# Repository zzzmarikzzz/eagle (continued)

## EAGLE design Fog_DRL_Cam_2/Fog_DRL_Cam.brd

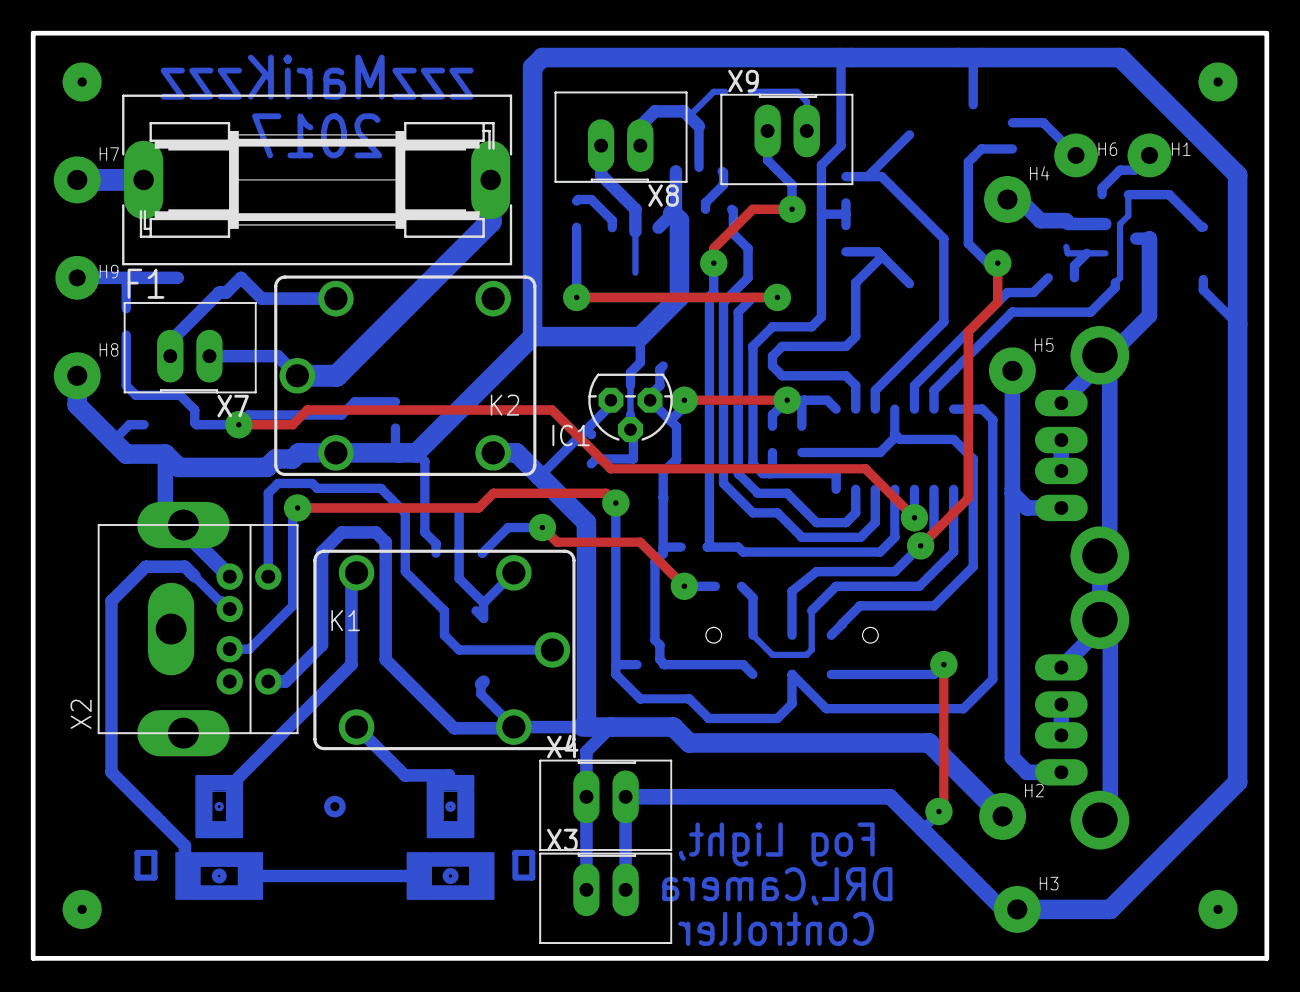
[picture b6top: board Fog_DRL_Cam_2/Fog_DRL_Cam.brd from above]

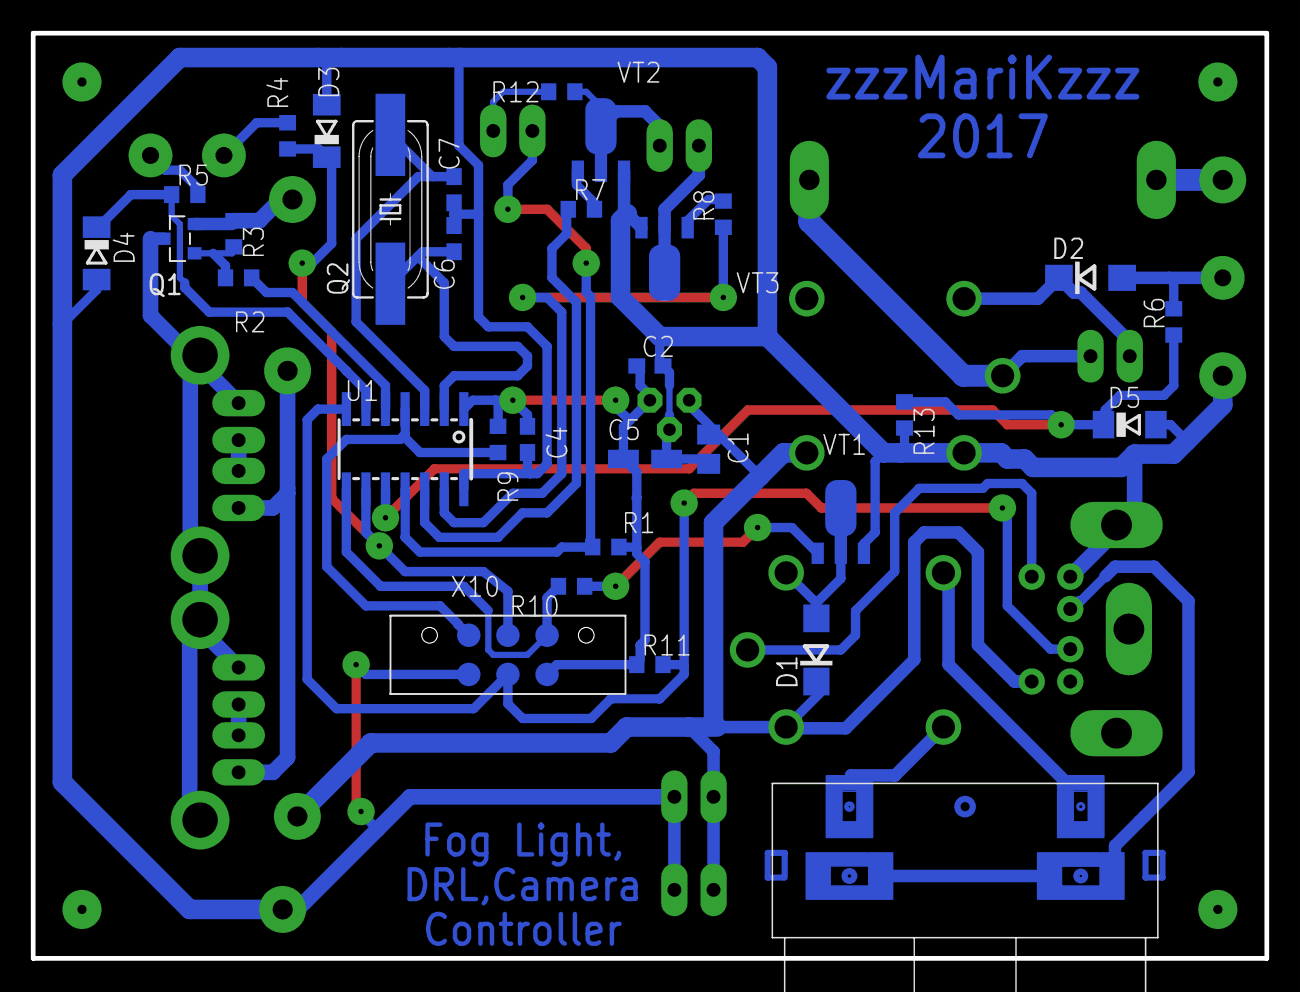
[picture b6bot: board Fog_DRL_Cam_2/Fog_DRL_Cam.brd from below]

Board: 2 copper layers, 80.0 x 60.0 mm, 53 parts (32 on the bottom side), 38 nets.

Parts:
C1: 330n; C0805
C2, C4: 100n; C0603
C5: 10uF; CT3216
C6, C7: 22pF; C0603
D1, D2: DIODESMD; DO214AC
D3, D4, D5: SOD80C
F1: SH22,5A
H1: Reverse; 2,8
H2: 12V; 3,0
H3, H4, H8: GND; 3,0
H5: 5V; 3,0
H6: Bliz; 2,8
H7: +12V; 3,0
H9: Mar; 2,8
IC1: 78L05Z; TO92
K1, K2: CQ1-12V; CQ1
Q1: IRLML2502; SOT-23-GSD
Q2: 16MHz; HC49UP
R1, R7, R8, R9, R10, R11, R13: 10k; R0603
R2: 220; R0603
R3: 47k; R0603
R4, R5, R6: 2k2; R0603
R12: 0R; R0603
U1: ATTINY24A-SU; SO14
VT1, VT2, VT3: BCX56-16; SOT89-BCE
X1: RCAX2
X2: PS/2
X3, X4, X7, X8, X9: JST2; JST*2
X5, X6: USB-FEMALE
X10: PROG-ISP6POGOPIN; PROG_POGOPIN

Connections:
+5V: C2.1, C4.1, C5.+, IC1.1, R1.2, R9.1, R11.1, U1.1, X10.2
+12V: C1.1, D1.C, H2.P$1, IC1.3, K1.1, K2.NO, X2.5, X3.1, X4.1
BLIZHNIY: D3.C, R4.1, U1.9, X10.3
CAM_RELAY: R10.1, U1.8, X10.1
GND: C1.2, C2.2, C4.2, C5.-, C6.2, C7.2, D3.A, D4.A, D5.A, H3.P$1, H8.P$1, IC1.2, K2.2, R13.2, U1.14, VT1.E, VT2.E, VT3.E, X2.4, X2.GND0, X3.2, X4.2, X10.6
GNDA: H4.P$1, Q1.S, R3.1
MAR: D5.C, R6.1, R13.1, U1.10
unnamed: K1.NO, X1.AV1
unnamed: R12.2, X9.2
unnamed: X1.GND1, X1.GND2, X2.2
unnamed: K1.C, X2.6
unnamed: D1.A, K1.2, VT1.C, VT1.C@1
unnamed: F1.1, H7.P$1
unnamed: H5.P$1, X5.VCC, X6.VCC
unnamed: Q1.D, X5.GND, X5.GND@1, X5.GND@2, X6.GND, X6.GND@1, X6.GND@2
unnamed: X5.D+, X5.D-
unnamed: X6.D+, X6.D-
unnamed: F1.2, K2.C, X7.1
unnamed: D2.C, K2.1, X7.2
unnamed: D2.A, H9.P$1, R6.2
unnamed: R2.1, U1.5
unnamed: VT3.C, VT3.C@1, X8.2
unnamed: R12.1, VT2.C, VT2.C@1, X8.1
unnamed: R8.1, U1.13
unnamed: R7.1, U1.12
unnamed: R1.1, U1.11, X9.1
unnamed: Q1.G, R2.2, R3.2
unnamed: H1.P$1, R5.2
unnamed: H6.P$1, R4.2
unnamed: R7.2, VT2.B
unnamed: R8.2, VT3.B
unnamed: C6.1, Q2.1, U1.2
unnamed: R10.2, VT1.B
unnamed: K1.NC, X1.AV2
unnamed: R9.2, U1.4, X10.5
unnamed: C7.1, Q2.2, U1.3
REVERSE: D4.C, R5.1, U1.6
REVERS_KEY: R11.2, U1.7, X2.1, X10.4

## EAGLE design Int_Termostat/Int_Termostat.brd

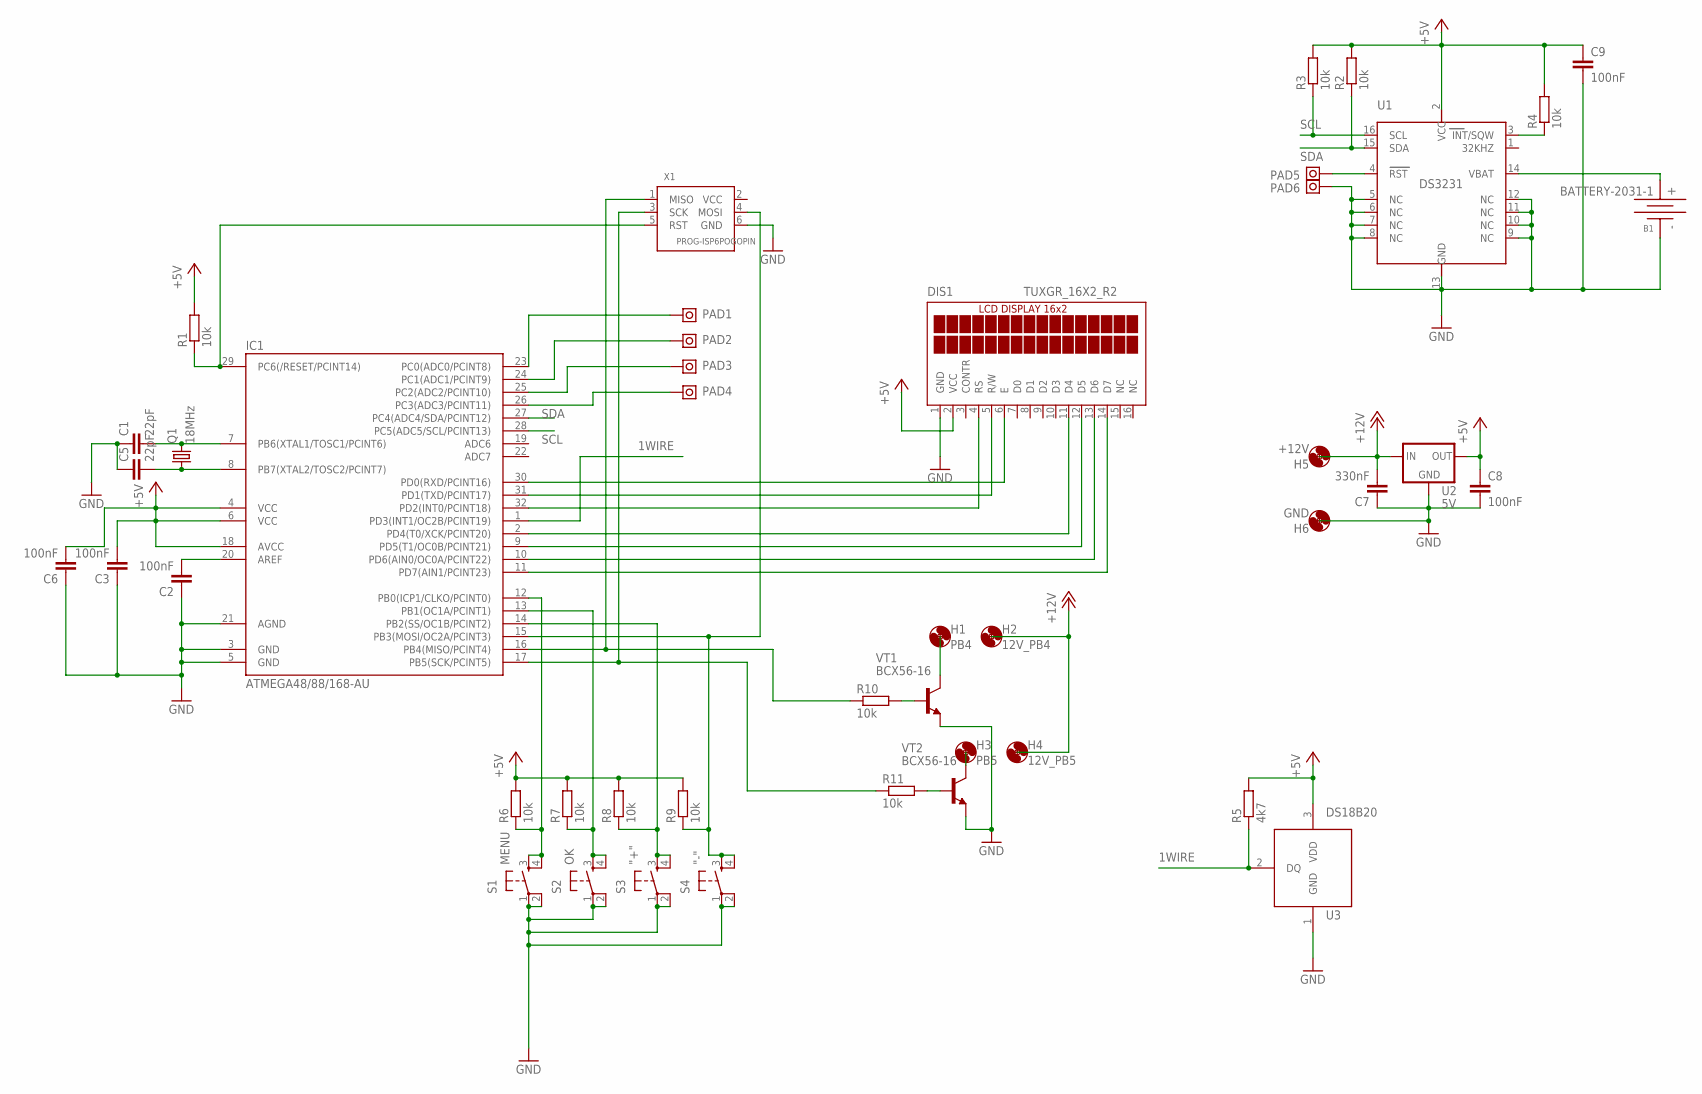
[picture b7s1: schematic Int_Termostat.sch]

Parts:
B1: BATTERY-2031-1; BTH2032-1
C1, C5: 22pF; C0805
C2, C3, C6, C8, C9: 100nF; C0805
C7: 330nF; C0805
DIS1: TUXGR_16X2_R2
H1: PB4; 3,0
H2: 12V_PB4; 3,0
H3: PB5; 3,0
H4: 12V_PB5; 3,0
H5: +12V; 3,0
H6: GND; 3,0
IC1: ATMEGA48/88/168-AU; TQFP32-08
PAD1: PC0; PAD
PAD2: PC1; PAD
PAD3: PC2; PAD
PAD4: PC3; PAD
PAD5, PAD6: RST; PAD
Q1: 18MHz; HC49/S
R1, R2, R3, R4, R6, R7, R8, R9, R10, R11: 10k; R0603
R5: 4k7; R0603
S1: MENU; DTS-6
S2: OK; DTS-6
S3: "+"; DTS-6
S4: "-"; DTS-6
U1: DS3231; SO16
U2: 5V; TO263
U3: DS18B20; TO92
VT1, VT2: BCX56-16; SOT89-ECB
X1: PROG-ISP6POGOPIN; PROG_POGOPIN

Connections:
1WIRE: IC1.1 (PD3(INT1/OC2B/PCINT19)), R5.1, U3.2 (DQ)
+5V: C3.2, C6.2, C8.1, C9.1, DIS1.2 (VCC), IC1.4 (VCC), IC1.6 (VCC), IC1.18 (AVCC), R1.2, R2.2, R3.2, R4.2, R5.2, R6.2, R7.2, R8.2, R9.2, U1.2 (VCC), U2.2 (OUT), U3.3 (VDD)
+12V: C7.2, H2.P$1, H4.P$1, H5.P$1, U2.1 (IN)
GND: B1.-, C1.1, C2.1, C3.1, C5.1, C6.1, C7.1, C8.2, C9.2, DIS1.1 (GND), H6.P$1, IC1.3 (GND), IC1.5 (GND), IC1.21 (AGND), PAD6.P$1, S1.1, S1.2, S2.1, S2.2, S3.1, S3.2, S4.1, S4.2, U1.5 (NC), U1.6 (NC), U1.7 (NC), U1.8 (NC), U1.9 (NC), U1.10 (NC), U1.11 (NC), U1.12 (NC), U1.13 (GND), U2.3 (GND), U3.1 (GND), VT1.E, VT2.E, X1.6 (GND)
unnamed: C1.2, IC1.7 (PB6(XTAL1/TOSC1/PCINT6)), Q1.2
unnamed: C5.2, IC1.8 (PB7(XTAL2/TOSC2/PCINT7)), Q1.1
unnamed: C2.2, IC1.20 (AREF)
unnamed: IC1.17 (PB5(SCK/PCINT5)), R11.1, X1.3 (SCK)
unnamed: IC1.16 (PB4(MISO/PCINT4)), R10.1, X1.1 (MISO)
unnamed: IC1.15 (PB3(MOSI/OC2A/PCINT3)), R9.1, S4.3, S4.4, X1.4 (MOSI)
unnamed: B1.+, U1.14 (VBAT)
unnamed: IC1.29 (PC6(/RESET/PCINT14)), R1.1, X1.5 (RST)
unnamed: R4.1, U1.3 (INT/SQW)
unnamed: DIS1.6 (E), IC1.30 (PD0(RXD/PCINT16))
unnamed: DIS1.5 (R/W), IC1.31 (PD1(TXD/PCINT17))
unnamed: DIS1.4 (RS), IC1.32 (PD2(INT0/PCINT18))
unnamed: DIS1.11 (D4), IC1.2 (PD4(T0/XCK/PCINT20))
unnamed: DIS1.12 (D5), IC1.9 (PD5(T1/OC0B/PCINT21))
unnamed: DIS1.13 (D6), IC1.10 (PD6(AIN0/OC0A/PCINT22))
unnamed: DIS1.14 (D7), IC1.11 (PD7(AIN1/PCINT23))
unnamed: PAD5.P$1, U1.4 (RST)
unnamed: IC1.12 (PB0(ICP1/CLKO/PCINT0)), R6.1, S1.3, S1.4
unnamed: IC1.13 (PB1(OC1A/PCINT1)), R7.1, S2.3, S2.4
unnamed: IC1.14 (PB2(SS/OC1B/PCINT2)), R8.1, S3.3, S3.4
unnamed: H3.P$1, VT2.C, VT2.C@1 (C)
unnamed: R10.2, VT1.B
unnamed: R11.2, VT2.B
unnamed: H1.P$1, VT1.C, VT1.C@1 (C)
unnamed: IC1.23 (PC0(ADC0/PCINT8)), PAD1.P$1
unnamed: IC1.24 (PC1(ADC1/PCINT9)), PAD2.P$1
unnamed: IC1.25 (PC2(ADC2/PCINT10)), PAD3.P$1
unnamed: IC1.26 (PC3(ADC3/PCINT11)), PAD4.P$1
SCL: IC1.28 (PC5(ADC5/SCL/PCINT13)), R3.1, U1.16 (SCL)
SDA: IC1.27 (PC4(ADC4/SDA/PCINT12)), R2.1, U1.15 (SDA)

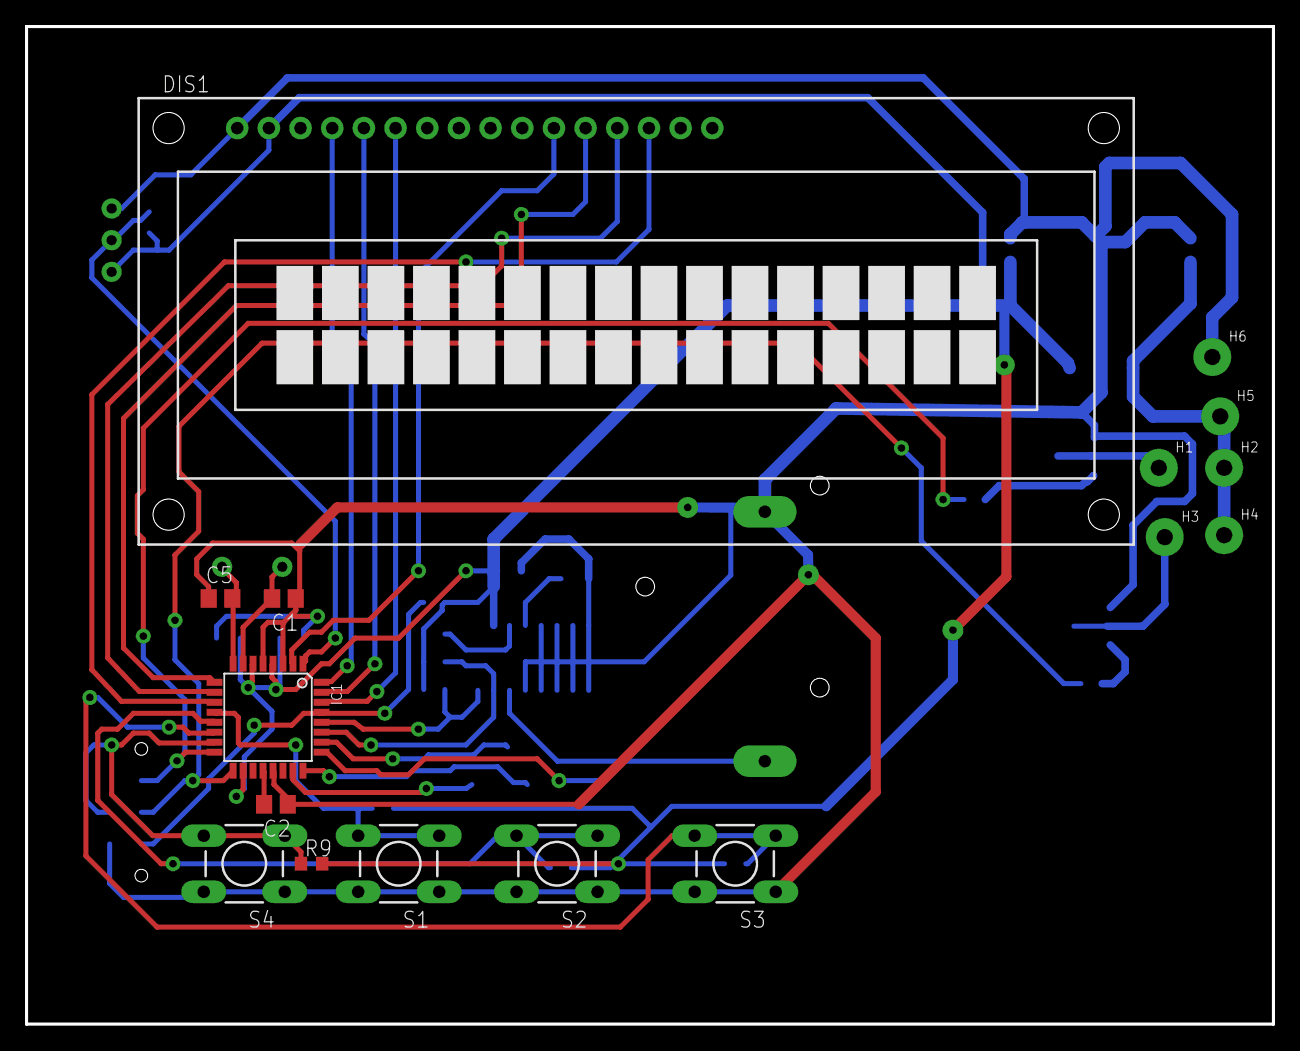
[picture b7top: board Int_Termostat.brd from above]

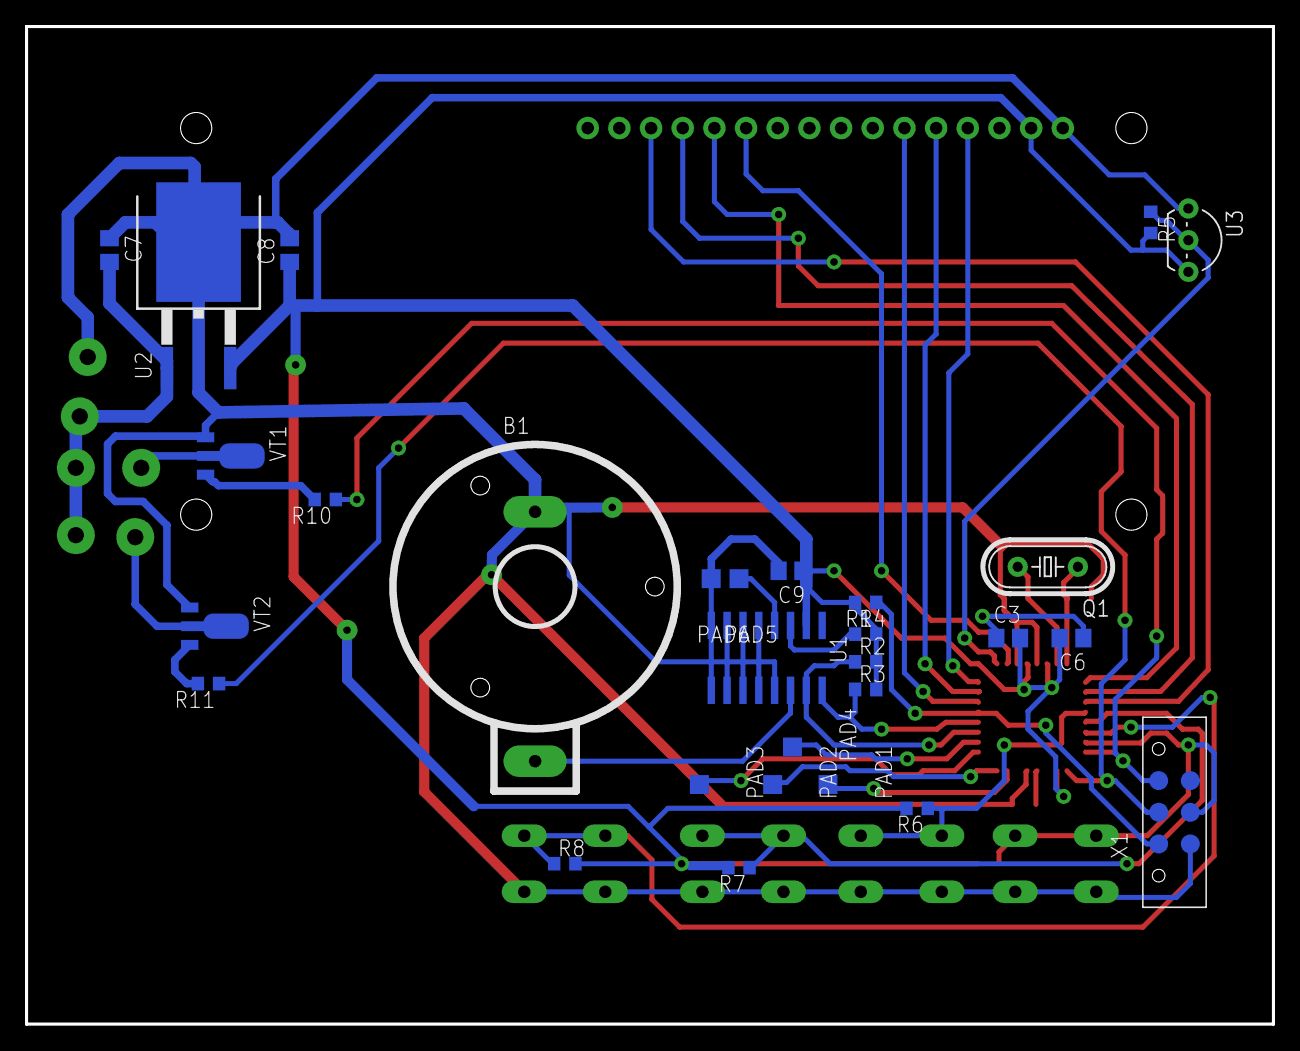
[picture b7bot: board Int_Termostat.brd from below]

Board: 2 copper layers, 100.0 x 80.0 mm, 45 parts (29 on the bottom side), 34 nets.

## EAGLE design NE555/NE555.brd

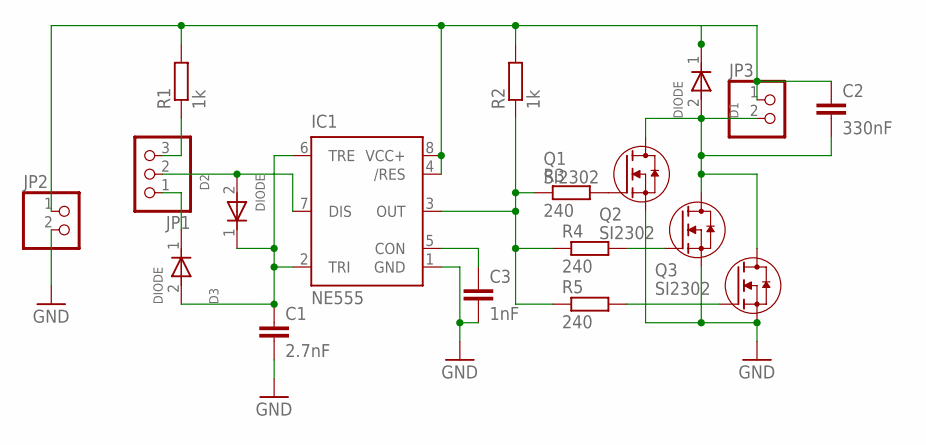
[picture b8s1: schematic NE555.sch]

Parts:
C1: 2.7nF; C0805
C2: 330nF; C0805
C3: 1nF; C0805
D1, D2, D3: DIODE; SOD80
IC1: NE555; SO08
JP1: PINHD-1X3; 1X03
JP2, JP3: PINHD-1X2; 1X02
Q1, Q2, Q3: SI2302; SOT-23-GSD
R1, R2: 1k; R0805
R3, R4, R5: 240; R0805

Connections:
GND: C1.2, C3.2, IC1.1 (GND), JP2.2, Q1.S, Q2.S, Q3.S
unnamed: C2.1, D1.1 (KATOD), IC1.4 (/RES), IC1.8 (VCC+), JP2.1, JP3.1, R1.2, R2.2
unnamed: IC1.3 (OUT), R2.1, R3.1, R4.1, R5.1
unnamed: C2.2, D1.2 (ANOD), JP3.2, Q1.D, Q2.D, Q3.D
unnamed: Q1.G, R3.2
unnamed: Q2.G, R4.2
unnamed: Q3.G, R5.2
unnamed: C3.1, IC1.5 (CON)
unnamed: C1.1, D2.1 (KATOD), D3.2 (ANOD), IC1.2 (TRI), IC1.6 (TRE)
unnamed: D2.2 (ANOD), IC1.7 (DIS), JP1.2
unnamed: JP1.3, R1.1
unnamed: D3.1 (KATOD), JP1.1

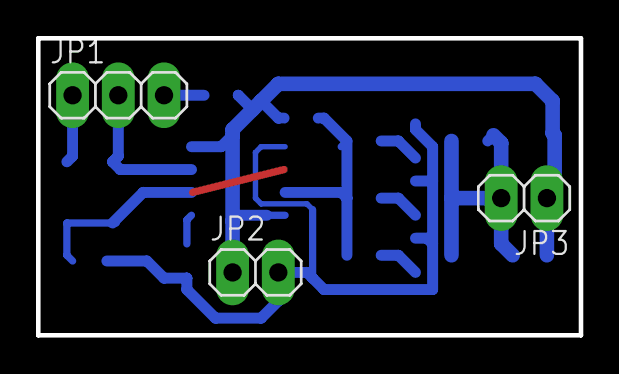
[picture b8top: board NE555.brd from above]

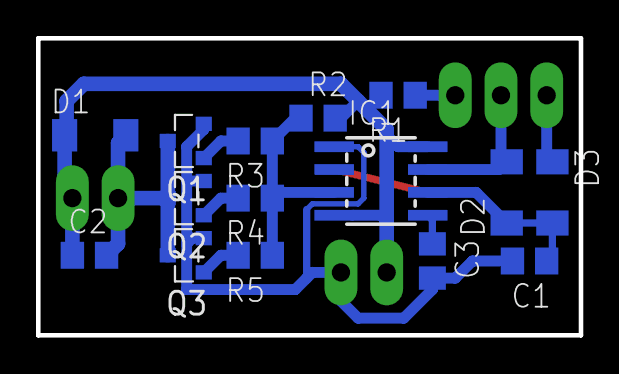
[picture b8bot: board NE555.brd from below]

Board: 2 copper layers, 30.1 x 16.5 mm, 18 parts (15 on the bottom side), 12 nets.
